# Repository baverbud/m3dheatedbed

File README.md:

# m3dheatedbed
DIY M3D heated printer bed

The logic board, firmware and app are not M3D specific, so this could be used with any printer. However, I have only tested it with the M3D.

Use at your own risk. Licensed under GPLv3.

Contents:
* app: Windows app to control temperature
* circuit: Schematic and PCB for the logic board. Use Kicad to open.
* firmware: Firmware for the atmega328p on the logic board. Uses atmel studio, but should be compatible with the Arduino toolchain.

Note that the firmware uses the Arduino PID Library at https://github.com/br3ttb/Arduino-PID-Library, which is licensed under the GPLv3 at the the time of this writing.

For a copy of the GPLv3, please see the LICENSE file.

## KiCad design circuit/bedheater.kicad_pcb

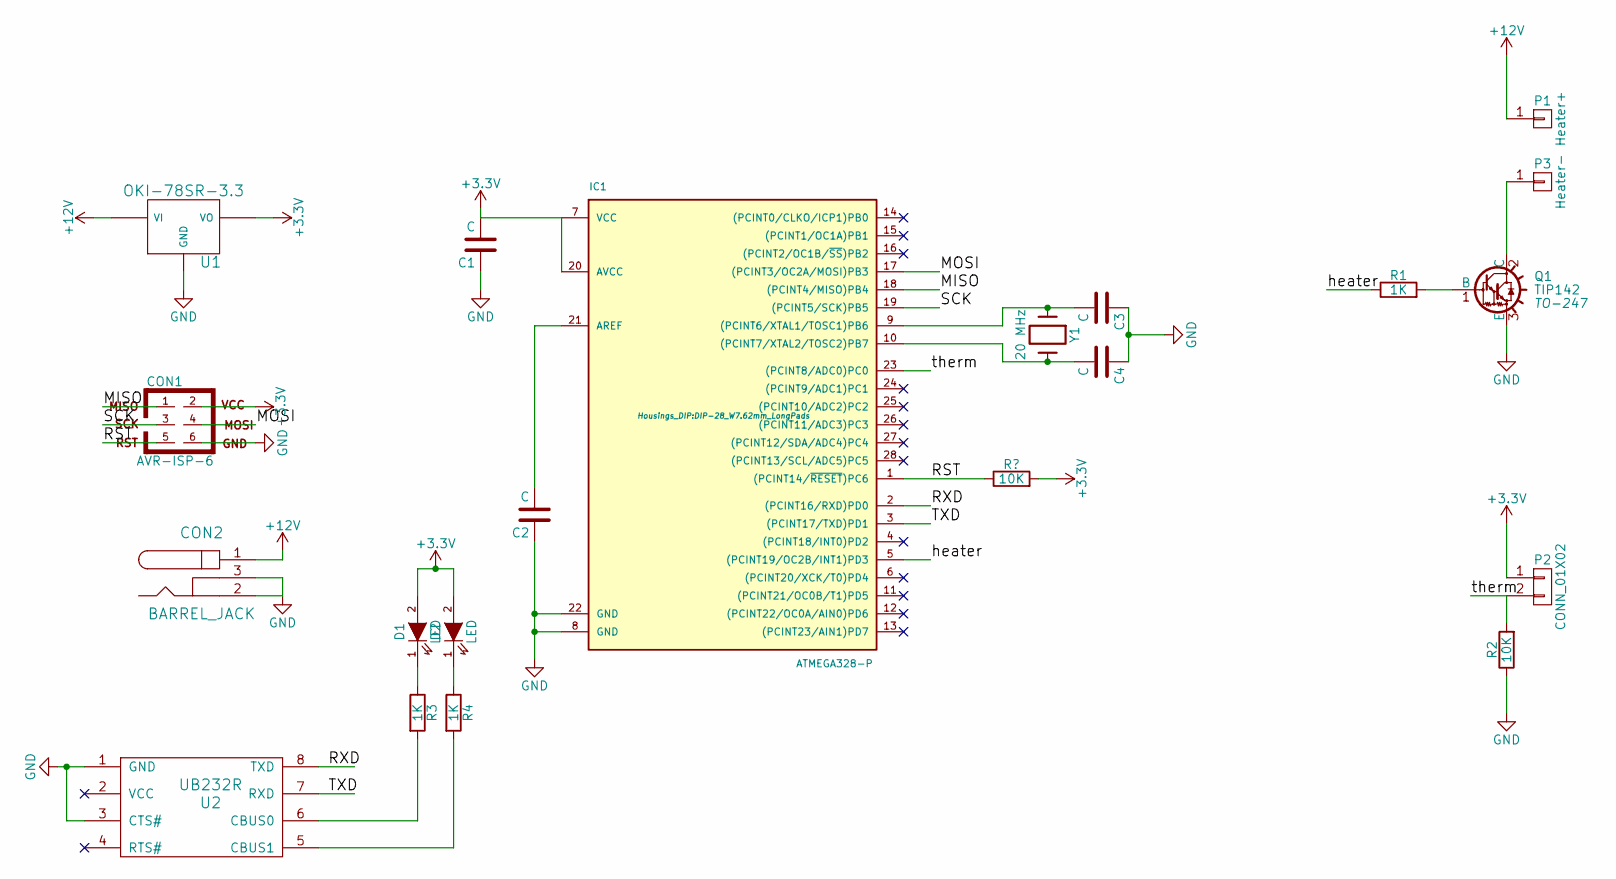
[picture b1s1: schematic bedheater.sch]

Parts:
C1, C2, C3, C4: C; C_Disc_D3_P2.5
CON1: AVR-ISP-6; Pin_Header_Straight_2x03
CON2: BARREL_JACK
D1, D2: LED
IC1: ATMEGA328-P; DIP-28_W7.62mm_LongPads
P1: Heater+; Banana_Jack_1Pin
P2: CONN_01X02; PINHEAD1-2
P3: Heater-; Banana_Jack_1Pin
Q1: TIP142; TO-247
R1, R3, R4: 1K; Resistor_Horizontal_RM10mm
R2: 10K; Resistor_Horizontal_RM10mm
U1: OKI-78SR-3.3; TO-220_Neutral123_Horizontal_Reverse_LargePads
U2: UB232R
Y1: 20 MHz; Crystal_HC49-U_Vertical

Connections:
+3V3: C1.2, CON1.2, D1.2 (A), D2.2 (A), IC1.7 (VCC), IC1.20 (AVCC), P2.1, U1.VO; also elsewhere on the board
+12V: CON2.1, P1.1, U1.VI
/MISO: CON1.1, IC1.18 ((PCINT4/MISO)PB4)
/MOSI: CON1.4, IC1.17 ((PCINT3/OC2A/MOSI)PB3)
/RST: CON1.5, IC1.1 ((PCINT14/~RESET~)PC6); also elsewhere on the board
/RXD: IC1.2 ((PCINT16/RXD)PD0), U2.8 (TXD)
/SCK: CON1.3, IC1.19 ((PCINT5/SCK)PB5)
/TXD: IC1.3 ((PCINT17/TXD)PD1), U2.7 (RXD)
/heater: IC1.5 ((PCINT19/OC2B/INT1)PD3), R1.1
/therm: IC1.23 ((PCINT8/ADC0)PC0), P2.2, R2.2
GND: C1.1, C2.1, C3.1, C4.1, CON1.6, CON2.2, CON2.3, IC1.8 (GND), IC1.22 (GND), Q1.3 (E), R2.1, U1.GND, U2.1 (GND), U2.3 (CTS#)
unnamed: C2.2, IC1.21 (AREF)
unnamed: C3.2, IC1.9 ((PCINT6/XTAL1/TOSC1)PB6), Y1.1
unnamed: C4.2, IC1.10 ((PCINT7/XTAL2/TOSC2)PB7), Y1.2
unnamed: D1.1 (K), R3.1
unnamed: D2.1 (K), R4.1
unnamed: P3.1, Q1.2 (C)
unnamed: Q1.1 (B), R1.2
unnamed: R3.2, U2.6 (CBUS0)
unnamed: R4.2, U2.5 (CBUS1)

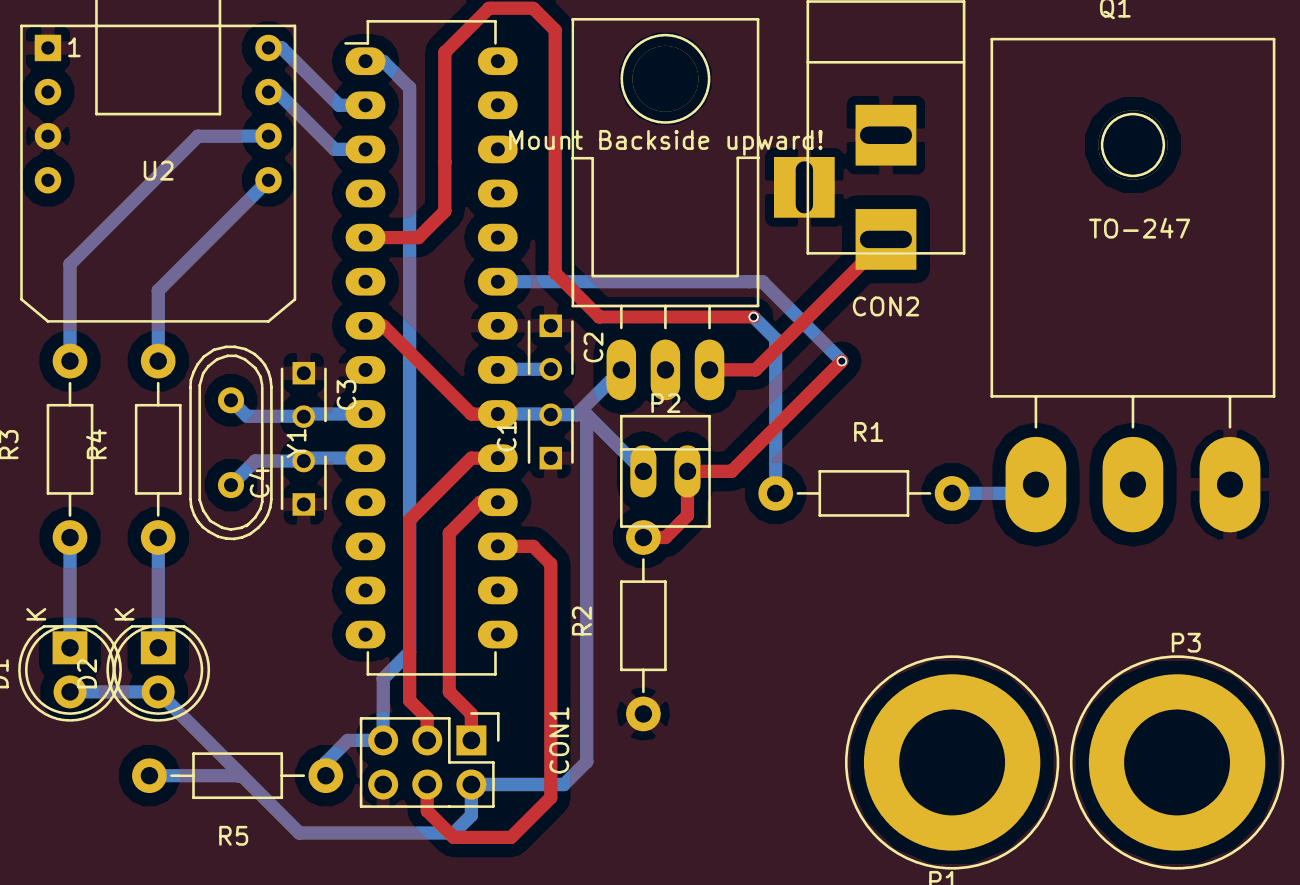
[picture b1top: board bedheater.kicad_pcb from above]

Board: 2 copper layers, 21 parts (0 on the bottom side), 20 nets.

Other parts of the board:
R5: 10K; Resistor_Horizontal_RM10mm

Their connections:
+3V3: R5.2; also elsewhere on the board
/RST: R5.1; also elsewhere on the board

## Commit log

2016-03-24 Update PID params. Fix schematic/pcb issue where the TIP142 was connected as though it were PNP (it is an NPN BJT). Correct some connectivity issues in the app
2016-03-24 Remove debug print. Save comPort to Settings before writing settings file
2016-03-24 Fix typo
